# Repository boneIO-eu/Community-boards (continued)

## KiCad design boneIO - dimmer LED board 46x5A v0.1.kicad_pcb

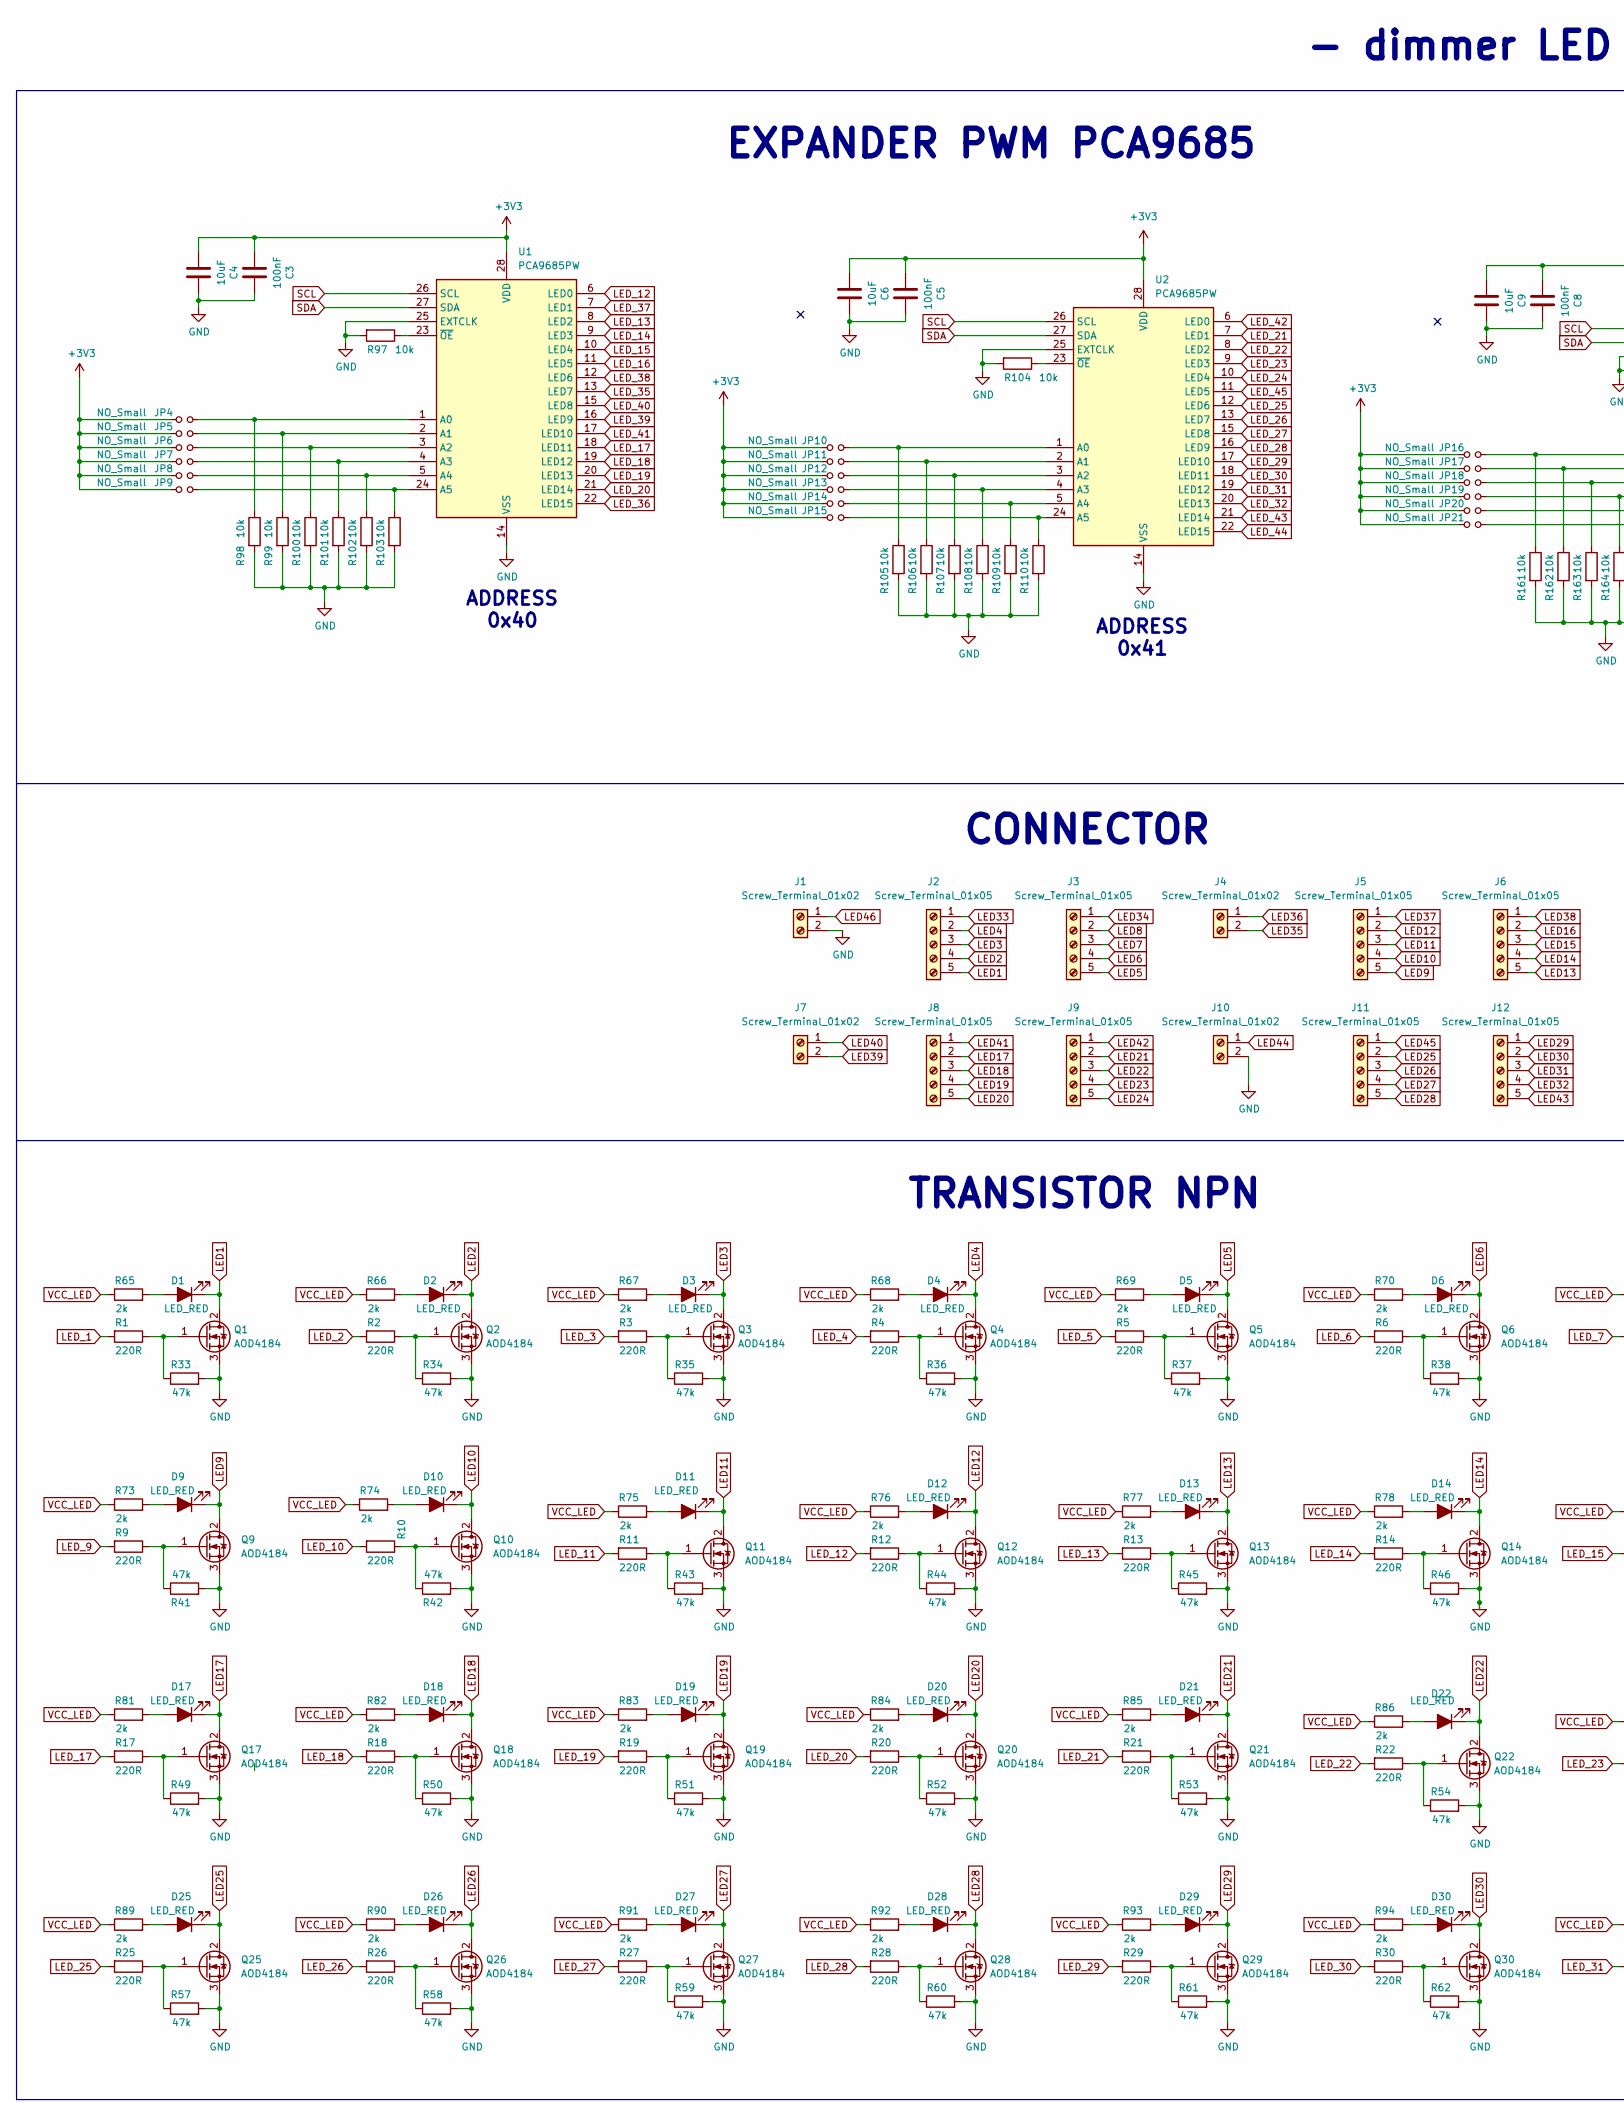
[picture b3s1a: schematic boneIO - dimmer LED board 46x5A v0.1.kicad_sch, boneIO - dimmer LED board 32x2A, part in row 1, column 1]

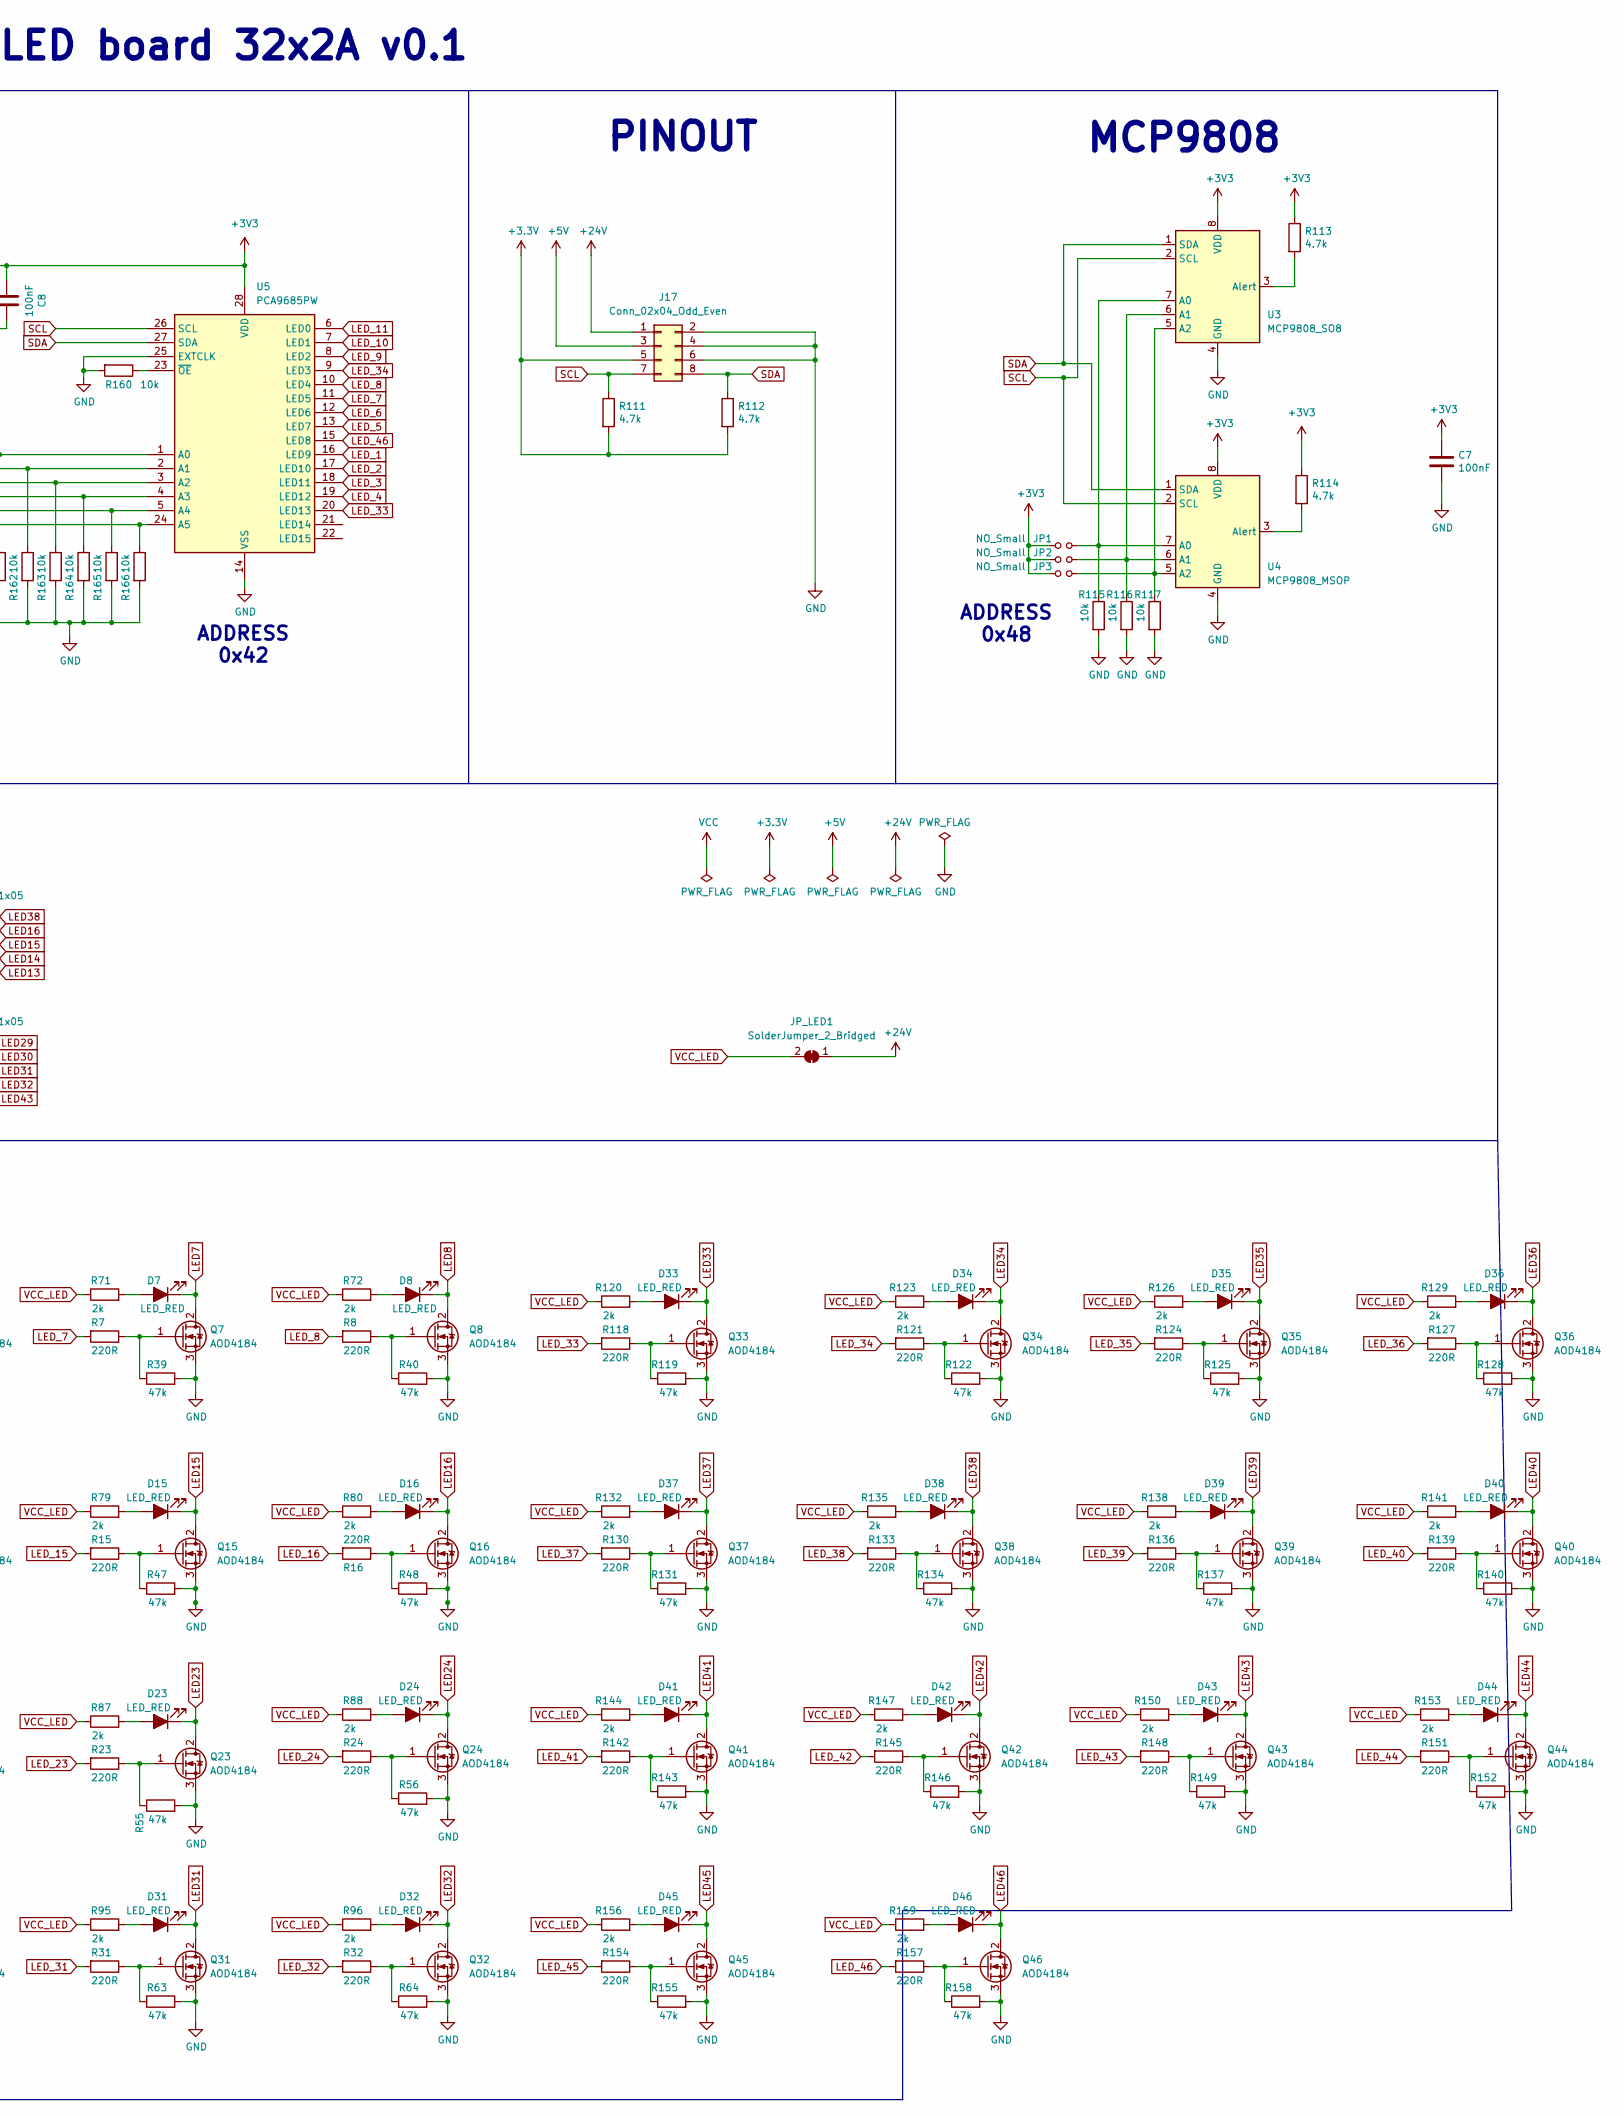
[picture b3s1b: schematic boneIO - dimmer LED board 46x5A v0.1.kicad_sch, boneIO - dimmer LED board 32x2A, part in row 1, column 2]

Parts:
C3, C5, C7, C8: 100nF; C_0603_1608Metric
C4, C6, C9: 10uF; C_0603_1608Metric
D1, D2, D3, D4, D5, D6, D7, D8, D9, D10, D11, D12, D13, D14, D15, D16, D17, D18, D19, D20, D21, D22, D23, D24, D25, D26, D27, D28, D29, D30, D31, D32, D33, D34, D35, D36, D37, D38, D39, D40, D41, D42, D43, D44, D45, D46: LED_RED; LED_0805_2012Metric; JLCPCB C84256
J1, J4, J7, J10: Screw_Terminal_01x02; PhoenixContact_GMSTBA_2,5_2-G_1x02_P7.50mm_Horizontal
J2, J3, J5, J6, J8, J9, J11, J12: Screw_Terminal_01x05; PhoenixContact_GMSTBA_2,5_5-G_1x05_P7.50mm_Horizontal
J17: Conn_02x04_Odd_Even; PinHeader_2x04_P2.54mm_Vertical
JP1, JP2, JP3, JP4, JP5, JP6, JP7, JP8, JP9, JP10, JP11, JP12, JP13, JP14, JP15, JP16, JP17, JP18, JP19, JP20, JP21: NO_Small; SolderJumper-2_P1.3mm_Open_RoundedPad1.0x1.5mm
JP_LED1: SolderJumper_2_Bridged; SolderJumper-2_P1.3mm_Bridged_RoundedPad1.0x1.5mm
Q1, Q2, Q3, Q4, Q5, Q6, Q7, Q8, Q9, Q10, Q11, Q12, Q13, Q14, Q15, Q16, Q17, Q18, Q19, Q20, Q21, Q22, Q23, Q24, Q25, Q26, Q27, Q28, Q29, Q30, Q31, Q32, Q33, Q34, Q35, Q36, Q37, Q38, Q39, Q40, Q41, Q42, Q43, Q44, Q45, Q46: AOD4184; TO-252-2
R1, R2, R3, R4, R5, R6, R7, R8, R9, R10, R11, R12, R13, R14, R15, R16, R17, R18, R19, R20, R21, R22, R23, R24, R25, R26, R27, R28, R29, R30, R31, R32, R118, R121, R124, R127, R130, R133, R136, R139, R142, R145, R148, R151, R154, R157: 220R; R_0603_1608Metric
R33, R34, R35, R36, R37, R38, R39, R40, R41, R42, R43, R44, R45, R46, R47, R48, R49, R50, R51, R52, R53, R54, R55, R56, R57, R58, R59, R60, R61, R62, R63, R64, R119, R122, R125, R128, R131, R134, R137, R140, R143, R146, R149, R152, R155, R158: 47k; R_0603_1608Metric
R65, R66, R67, R68, R69, R70, R71, R72, R73, R74, R75, R76, R77, R78, R79, R80, R81, R82, R83, R84, R85, R86, R87, R88, R89, R90, R91, R92, R93, R94, R95, R96, R120, R123, R126, R129, R132, R135, R138, R141, R144, R147, R150, R153, R156, R159: 2k; R_0603_1608Metric
R97, R98, R99, R100, R101, R102, R103, R104, R105, R106, R107, R108, R109, R110, R115, R116, R117, R160, R161, R162, R163, R164, R165, R166: 10k; R_0603_1608Metric
R111, R112, R113, R114: 4.7k; R_0603_1608Metric
U1, U2, U5: PCA9685PW; TSSOP-28_4.4x9.7mm_P0.65mm
U3: MCP9808_SO8; SO-8_3.9x4.9mm_P1.27mm
U4: MCP9808_MSOP; MSOP-8_3x3mm_P0.65mm

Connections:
+5V: J17.3
+24V: J17.1, JP_LED1.1 (A)
GND: C3.1, C4.1, C5.1, C6.1, C7.2, C8.1, C9.1, J1.2, J10.2, J17.2, J17.4, J17.6, Q1.3 (S), Q2.3 (S), Q3.3 (S), Q4.3 (S), Q5.3 (S), Q6.3 (S), Q7.3 (S), Q8.3 (S), Q9.3 (S), Q10.3 (S), Q11.3 (S), Q12.3 (S), Q13.3 (S), Q14.3 (S), Q15.3 (S), Q16.3 (S), Q17.3 (S), Q18.3 (S), Q19.3 (S), Q20.3 (S), Q21.3 (S), Q22.3 (S), Q23.3 (S), Q24.3 (S), Q25.3 (S), Q26.3 (S), Q27.3 (S), Q28.3 (S), Q29.3 (S), Q30.3 (S), Q31.3 (S), Q32.3 (S), Q33.3 (S), Q34.3 (S), Q35.3 (S), Q36.3 (S), Q37.3 (S), Q38.3 (S), Q39.3 (S), Q40.3 (S), Q41.3 (S), Q42.3 (S), Q43.3 (S), Q44.3 (S), Q45.3 (S), Q46.3 (S), R33.2, R34.2, R35.2, R36.2, R37.2, R38.2, R39.2, R40.2, R41.2, R42.2, R43.2, R44.2, R45.2, R46.2, R47.2, R48.2, R49.2, R50.2, R51.2, R52.2, R53.2, R54.2, R55.2, R56.2, R57.2, R58.2, R59.2, R60.2, R61.2, R62.2, R63.2, R64.2, R97.2, R98.2, R99.2, R100.2, R101.2, R102.2, R103.2, R104.2, R105.2, R106.2, R107.2, R108.2, R109.2, R110.2, R115.2, R116.2, R117.2, R119.2, R122.2, R125.2, R128.2, R131.2, R134.2, R137.2, R140.2, R143.2, R146.2, R149.2, R152.2, R155.2, R158.2, R160.2, R161.2, R162.2, R163.2, R164.2, R165.2, R166.2, U1.14 (VSS), U1.25 (EXTCLK), U2.14 (VSS), U2.25 (EXTCLK), U3.4 (GND), U4.4 (GND), U5.14 (VSS), U5.25 (EXTCLK)
LED1: D1.1 (K), J2.5, Q1.2 (D)
LED2: D2.1 (K), J2.4, Q2.2 (D)
LED3: D3.1 (K), J2.3, Q3.2 (D)
LED4: D4.1 (K), J2.2, Q4.2 (D)
LED5: D5.1 (K), J3.5, Q5.2 (D)
LED6: D6.1 (K), J3.4, Q6.2 (D)
LED7: D7.1 (K), J3.3, Q7.2 (D)
LED8: D8.1 (K), J3.2, Q8.2 (D)
LED9: D9.1 (K), J5.5, Q9.2 (D)
LED10: D10.1 (K), J5.4, Q10.2 (D)
LED11: D11.1 (K), J5.3, Q11.2 (D)
LED12: D12.1 (K), J5.2, Q12.2 (D)
LED13: D13.1 (K), J6.5, Q13.2 (D)
LED14: D14.1 (K), J6.4, Q14.2 (D)
LED15: D15.1 (K), J6.3, Q15.2 (D)
LED16: D16.1 (K), J6.2, Q16.2 (D)
LED17: D17.1 (K), J8.2, Q17.2 (D)
LED18: D18.1 (K), J8.3, Q18.2 (D)
LED19: D19.1 (K), J8.4, Q19.2 (D)
LED20: D20.1 (K), J8.5, Q20.2 (D)
LED21: D21.1 (K), J9.2, Q21.2 (D)
LED22: D22.1 (K), J9.3, Q22.2 (D)
LED23: D23.1 (K), J9.4, Q23.2 (D)
LED24: D24.1 (K), J9.5, Q24.2 (D)
LED25: D25.1 (K), J11.2, Q25.2 (D)
LED26: D26.1 (K), J11.3, Q26.2 (D)
LED27: D27.1 (K), J11.4, Q27.2 (D)
LED28: D28.1 (K), J11.5, Q28.2 (D)
LED29: D29.1 (K), J12.1, Q29.2 (D)
LED30: D30.1 (K), J12.2, Q30.2 (D)
LED31: D31.1 (K), J12.3, Q31.2 (D)
LED32: D32.1 (K), J12.4, Q32.2 (D)
LED33: D33.1 (K), J2.1, Q33.2 (D)
LED34: D34.1 (K), J3.1, Q34.2 (D)
LED35: D35.1 (K), J4.2, Q35.2 (D)
LED36: D36.1 (K), J4.1, Q36.2 (D)
LED37: D37.1 (K), J5.1, Q37.2 (D)
LED38: D38.1 (K), J6.1, Q38.2 (D)
LED39: D39.1 (K), J7.2, Q39.2 (D)
LED40: D40.1 (K), J7.1, Q40.2 (D)
LED41: D41.1 (K), J8.1, Q41.2 (D)
LED42: D42.1 (K), J9.1, Q42.2 (D)
LED43: D43.1 (K), J12.5, Q43.2 (D)
LED44: D44.1 (K), J10.1, Q44.2 (D)
LED45: D45.1 (K), J11.1, Q45.2 (D)
LED46: D46.1 (K), J1.1, Q46.2 (D)
LED_1: R1.2, U5.16 (LED9)
LED_2: R2.2, U5.17 (LED10)
LED_3: R3.2, U5.18 (LED11)
LED_4: R4.2, U5.19 (LED12)
LED_5: R5.2, U5.13 (LED7)
LED_6: R6.2, U5.12 (LED6)
LED_7: R7.2, U5.11 (LED5)
LED_8: R8.2, U5.10 (LED4)
LED_9: R9.2, U5.8 (LED2)
LED_10: R10.2, U5.7 (LED1)
LED_11: R11.2, U5.6 (LED0)
LED_12: R12.2, U1.6 (LED0)
LED_13: R13.2, U1.8 (LED2)
LED_14: R14.2, U1.9 (LED3)
LED_15: R15.2, U1.10 (LED4)
LED_16: R16.2, U1.11 (LED5)
LED_17: R17.2, U1.18 (LED11)
LED_18: R18.2, U1.19 (LED12)
LED_19: R19.2, U1.20 (LED13)
LED_20: R20.2, U1.21 (LED14)
LED_21: R21.2, U2.7 (LED1)
LED_22: R22.2, U2.8 (LED2)
LED_23: R23.2, U2.9 (LED3)
LED_24: R24.2, U2.10 (LED4)
LED_25: R25.2, U2.12 (LED6)
LED_26: R26.2, U2.13 (LED7)
LED_27: R27.2, U2.15 (LED8)
LED_28: R28.2, U2.16 (LED9)
LED_29: R29.2, U2.17 (LED10)
LED_30: R30.2, U2.18 (LED11)
LED_31: R31.2, U2.19 (LED12)
LED_32: R32.2, U2.20 (LED13)
LED_33: R118.2, U5.20 (LED13)
LED_34: R121.2, U5.9 (LED3)
LED_35: R124.2, U1.13 (LED7)
LED_36: R127.2, U1.22 (LED15)
LED_37: R130.2, U1.7 (LED1)
LED_38: R133.2, U1.12 (LED6)
LED_39: R136.2, U1.16 (LED9)
LED_40: R139.2, U1.15 (LED8)
LED_41: R142.2, U1.17 (LED10)
LED_42: R145.2, U2.6 (LED0)
LED_43: R148.2, U2.21 (LED14)
LED_44: R151.2, U2.22 (LED15)
LED_45: R154.2, U2.11 (LED5)
LED_46: R157.2, U5.15 (LED8)
unnamed: D1.2 (A), R65.2
unnamed: D2.2 (A), R66.2
unnamed: D3.2 (A), R67.2
unnamed: D4.2 (A), R68.2
unnamed: D5.2 (A), R69.2
unnamed: D6.2 (A), R70.2
unnamed: D7.2 (A), R71.2
unnamed: D8.2 (A), R72.2
unnamed: D9.2 (A), R73.2
unnamed: D10.2 (A), R74.2
unnamed: D11.2 (A), R75.2
unnamed: D12.2 (A), R76.2
unnamed: D13.2 (A), R77.2
unnamed: D14.2 (A), R78.2
unnamed: D15.2 (A), R79.2
unnamed: D16.2 (A), R80.2
unnamed: D17.2 (A), R81.2
unnamed: D18.2 (A), R82.2
unnamed: D19.2 (A), R83.2
unnamed: D20.2 (A), R84.2
unnamed: D21.2 (A), R85.2
unnamed: D22.2 (A), R86.2
unnamed: D23.2 (A), R87.2
unnamed: D24.2 (A), R88.2
unnamed: D25.2 (A), R89.2
unnamed: D26.2 (A), R90.2
unnamed: D27.2 (A), R91.2
unnamed: D28.2 (A), R92.2
unnamed: D29.2 (A), R93.2
unnamed: D30.2 (A), R94.2
unnamed: D31.2 (A), R95.2
unnamed: D32.2 (A), R96.2
unnamed: D33.2 (A), R120.2
unnamed: D34.2 (A), R123.2
unnamed: D35.2 (A), R126.2
unnamed: D36.2 (A), R129.2
unnamed: D37.2 (A), R132.2
unnamed: D38.2 (A), R135.2
unnamed: D39.2 (A), R138.2
unnamed: D40.2 (A), R141.2
unnamed: D41.2 (A), R144.2
unnamed: D42.2 (A), R147.2
unnamed: D43.2 (A), R150.2
unnamed: D44.2 (A), R153.2
unnamed: D45.2 (A), R156.2
unnamed: D46.2 (A), R159.2
unnamed: JP1.2, R115.1, U3.7 (A0), U4.7 (A0)
unnamed: JP2.2, R116.1, U3.6 (A1), U4.6 (A1)
unnamed: JP3.2, R117.1, U3.5 (A2), U4.5 (A2)
unnamed: JP4.2, R98.1, U1.1 (A0)
unnamed: JP5.2, R99.1, U1.2 (A1)
unnamed: JP6.2, R100.1, U1.3 (A2)
unnamed: JP7.2, R101.1, U1.4 (A3)
unnamed: JP8.2, R102.1, U1.5 (A4)
unnamed: JP9.2, R103.1, U1.24 (A5)
unnamed: JP10.2, R105.1, U2.1 (A0)
unnamed: JP11.2, R106.1, U2.2 (A1)
unnamed: JP12.2, R107.1, U2.3 (A2)
unnamed: JP13.2, R108.1, U2.4 (A3)
unnamed: JP14.2, R109.1, U2.5 (A4)
unnamed: JP15.2, R110.1, U2.24 (A5)
unnamed: JP16.2, R161.1, U5.1 (A0)
unnamed: JP17.2, R162.1, U5.2 (A1)
unnamed: JP18.2, R163.1, U5.3 (A2)
unnamed: JP19.2, R164.1, U5.4 (A3)
unnamed: JP20.2, R165.1, U5.5 (A4)
unnamed: JP21.2, R166.1, U5.24 (A5)
unnamed: Q1.1 (G), R1.1, R33.1
unnamed: Q2.1 (G), R2.1, R34.1
unnamed: Q3.1 (G), R3.1, R35.1
unnamed: Q4.1 (G), R4.1, R36.1
unnamed: Q5.1 (G), R5.1, R37.1
unnamed: Q6.1 (G), R6.1, R38.1
unnamed: Q7.1 (G), R7.1, R39.1
unnamed: Q8.1 (G), R8.1, R40.1
unnamed: Q9.1 (G), R9.1, R41.1
unnamed: Q10.1 (G), R10.1, R42.1
unnamed: Q11.1 (G), R11.1, R43.1
unnamed: Q12.1 (G), R12.1, R44.1
unnamed: Q13.1 (G), R13.1, R45.1
unnamed: Q14.1 (G), R14.1, R46.1
unnamed: Q15.1 (G), R15.1, R47.1
unnamed: Q16.1 (G), R16.1, R48.1
unnamed: Q17.1 (G), R17.1, R49.1
unnamed: Q18.1 (G), R18.1, R50.1
unnamed: Q19.1 (G), R19.1, R51.1
unnamed: Q20.1 (G), R20.1, R52.1
unnamed: Q21.1 (G), R21.1, R53.1
unnamed: Q22.1 (G), R22.1, R54.1
unnamed: Q23.1 (G), R23.1, R55.1
unnamed: Q24.1 (G), R24.1, R56.1
unnamed: Q25.1 (G), R25.1, R57.1
unnamed: Q26.1 (G), R26.1, R58.1
unnamed: Q27.1 (G), R27.1, R59.1
unnamed: Q28.1 (G), R28.1, R60.1
unnamed: Q29.1 (G), R29.1, R61.1
unnamed: Q30.1 (G), R30.1, R62.1
unnamed: Q31.1 (G), R31.1, R63.1
unnamed: Q32.1 (G), R32.1, R64.1
unnamed: Q33.1 (G), R118.1, R119.1
unnamed: Q34.1 (G), R121.1, R122.1
unnamed: Q35.1 (G), R124.1, R125.1
unnamed: Q36.1 (G), R127.1, R128.1
unnamed: Q37.1 (G), R130.1, R131.1
unnamed: Q38.1 (G), R133.1, R134.1
unnamed: Q39.1 (G), R136.1, R137.1
unnamed: Q40.1 (G), R139.1, R140.1
unnamed: Q41.1 (G), R142.1, R143.1
unnamed: Q42.1 (G), R145.1, R146.1
unnamed: Q43.1 (G), R148.1, R149.1
unnamed: Q44.1 (G), R151.1, R152.1
unnamed: Q45.1 (G), R154.1, R155.1
unnamed: Q46.1 (G), R157.1, R158.1
unnamed: R97.1, U1.23 (~OE)
unnamed: R104.1, U2.23 (~OE)
unnamed: R113.2, U3.3 (Alert)
unnamed: R114.2, U4.3 (Alert)
unnamed: R160.1, U5.23 (~OE)
SCL: J17.7, R111.1, U1.26 (SCL), U2.26 (SCL), U3.2 (SCL), U4.2 (SCL), U5.26 (SCL)
SDA: J17.8, R112.1, U1.27 (SDA), U2.27 (SDA), U3.1 (SDA), U4.1 (SDA), U5.27 (SDA)
VCC_LED: JP_LED1.2 (B), R65.1, R66.1, R67.1, R68.1, R69.1, R70.1, R71.1, R72.1, R73.1, R74.1, R75.1, R76.1, R77.1, R78.1, R79.1, R80.1, R81.1, R82.1, R83.1, R84.1, R85.1, R86.1, R87.1, R88.1, R89.1, R90.1, R91.1, R92.1, R93.1, R94.1, R95.1, R96.1, R120.1, R123.1, R126.1, R129.1, R132.1, R135.1, R138.1, R141.1, R144.1, R147.1, R150.1, R153.1, R156.1, R159.1

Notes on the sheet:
PINOUT
ADDRESS 0x42
TRANSISTOR NPN
- dimmer LED board 32x2A v0.1
ADDRESS 0x40
ADDRESS 0x41
ADDRESS 0x48
MCP9808
EXPANDER PWM PCA9685
CONNECTOR

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
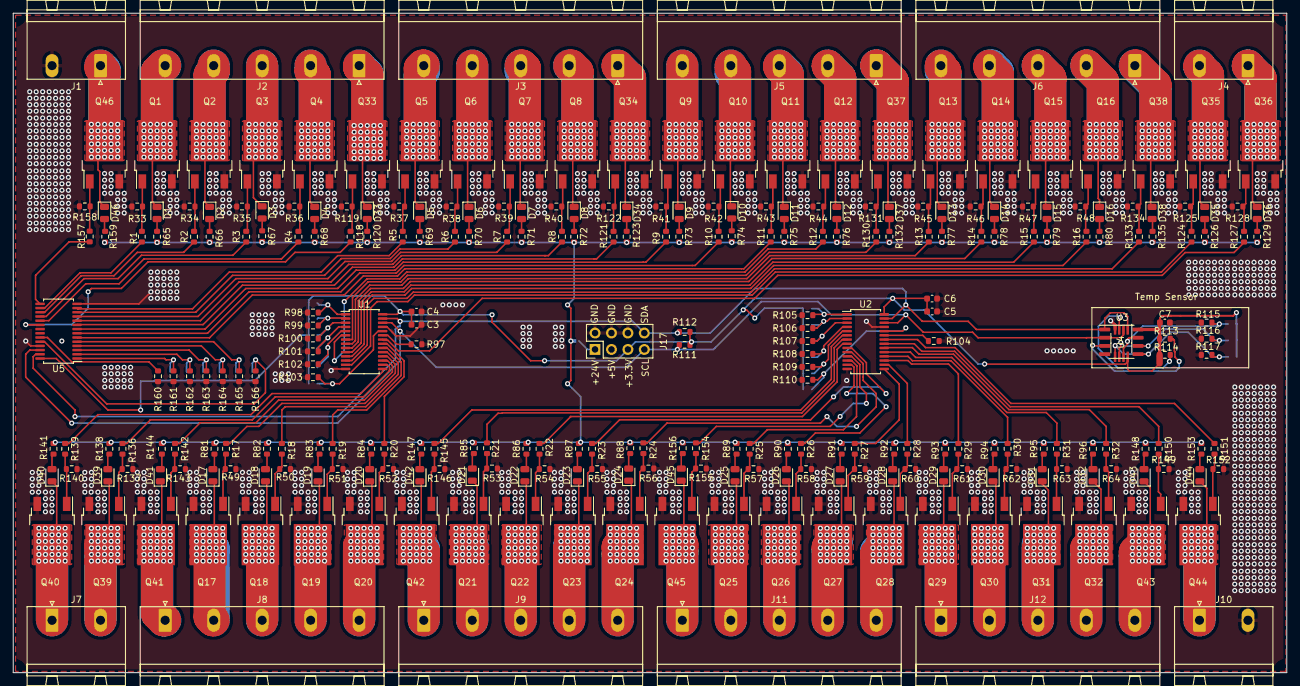
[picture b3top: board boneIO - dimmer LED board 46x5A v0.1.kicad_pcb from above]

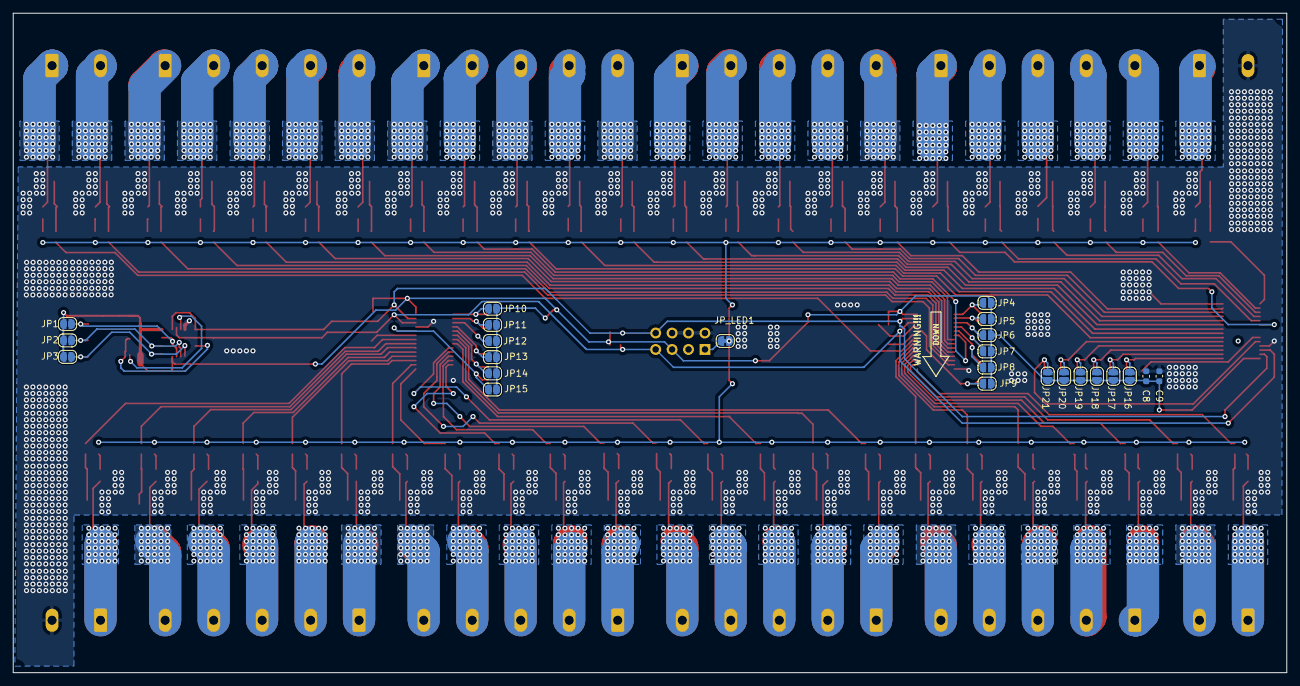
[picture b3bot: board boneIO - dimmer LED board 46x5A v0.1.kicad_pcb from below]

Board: 2 copper layers, 197.0 x 102.0 mm, 305 parts (24 on the bottom side), 216 nets.

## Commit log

2022-10-07 version 0.1 - to be reviewed
2022-10-09 rename repo to community boards
2022-12-30 Expansion module WT32-ETH01
    Expansion module made on WT32-ETH01
2023-01-17 rename doc to docs
2023-04-12 dimmer_board_4x4A_v0.1.0
2023-04-12 add GND
2023-04-14 przesuniecie zlaczy
2023-05-08 add external board
